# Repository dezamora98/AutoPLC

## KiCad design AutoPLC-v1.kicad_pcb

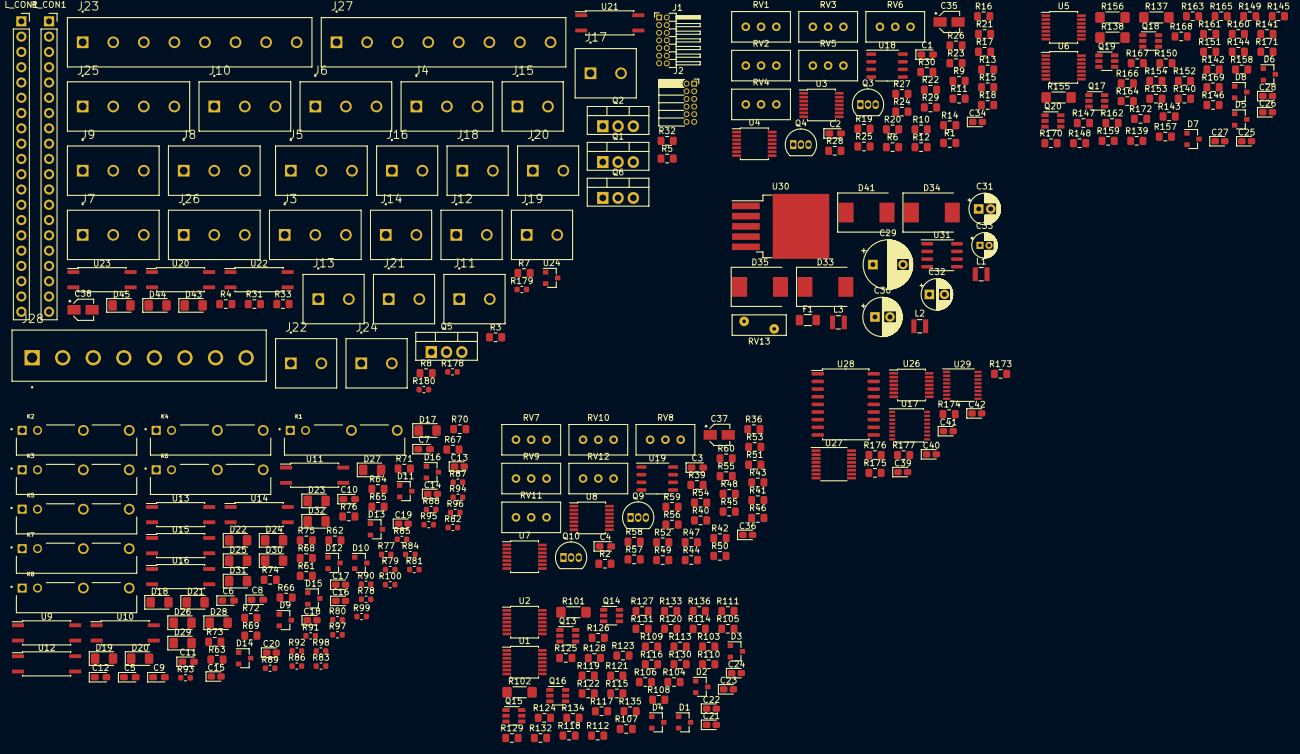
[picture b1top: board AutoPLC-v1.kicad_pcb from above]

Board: 2 copper layers, 358 parts (0 on the bottom side), 318 nets, no tracks yet.

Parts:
C1, C2, C3: 1u; CP_EIA-2012-15_AVX-P_Pad1.30x1.05mm_HandSolder
C4: 2u; CP_EIA-2012-15_AVX-P_Pad1.30x1.05mm_HandSolder
C5, C6, C7, C8, C9, C10, C11, C12: C; CP_EIA-2012-15_AVX-P_Pad1.30x1.05mm_HandSolder
C13, C14, C15, C16, C17, C18, C19, C20: C; CP_EIA-1608-10_AVX-L_Pad1.25x1.05mm_HandSolder
C21, C22, C23, C24, C25, C26, C27, C28: 100n; CP_EIA-1608-10_AVX-L_Pad1.25x1.05mm_HandSolder
C29: 100uF; CP_Radial_D8.0mm_P5.00mm
C30: 220uF; CP_Radial_D6.3mm_P2.50mm
C31: 10uF; CP_Radial_D5.0mm_P2.00mm
C32: 100uF; CP_Radial_D5.0mm_P2.50mm
C33: 10uF; CP_Radial_D4.0mm_P1.50mm
C34, C36, C39, C40, C41, C42: 0.1u; CP_EIA-1608-08_AVX-J_Pad1.25x1.05mm_HandSolder
C35, C37, C38: 10u; CP_Elec_3x5.3
D1, D2, D3, D4, D5, D6, D7, D8: 5v; SOT-23
D9, D10, D11, D12, D13, D14, D15, D16: 1.5; SOT-23
D17, D18, D19, D20, D21, D22, D23, D24, D25, D26, D27, D28, D29, D30, D31, D32: LED; LED_1206_3216Metric_Pad1.42x1.75mm_HandSolder
D33, D34, D35, D41: B360; D_SMC
D43: LED_C; LED_1206_3216Metric_Pad1.42x1.75mm_HandSolder
D44: LED_P; LED_1206_3216Metric_Pad1.42x1.75mm_HandSolder
D45: LED_R; LED_1206_3216Metric_Pad1.42x1.75mm_HandSolder
F1: 3A; Fuse_1206_3216Metric
J1: P_EXP; PinHeader_2x07_P1.27mm_Horizontal
J2: P_ET_MOD; PinSocket_2x06_P1.27mm_Horizontal
J3: AIN_1; BORNERAS_3
J4: AIN_2; BORNERAS_3
J5: AIN_3; BORNERAS_3
J6: AIN_4; BORNERAS_3
J7: AIN_5; BORNERAS_3
J8: AIN_6; BORNERAS_3
J9: AIN_7; BORNERAS_3
J10: AIN_8; BORNERAS_3
J11, J14, J17, J20: AOUT_V; BORNERAS_2
J12, J15, J18, J21: AOUT_C; BORNERAS_2
J13: OUT_T1; BORNERAS_2
J16: OUT_T2; BORNERAS_2
J19: OUT_T3; BORNERAS_2
J22: OUT_T4; BORNERAS_2
J23: DIN; BORNERAS_8
J24: PW_IN; BORNERAS_2
J25: PW & D_COM; BORNERAS_4
J26: PW_OUT_1; BORNERAS_3
J27: R-out; BORNERAS_8
J28: R-out; P_BORNERAS_8
K1, K2, K3, K4, K5, K6, K7, K8: Relay; r
L1, L3: 20uH; L_Wuerth_MAPI-2512
L2: 33uH; L_Wuerth_MAPI-2512
L_CON1: Conn_01x20_Male; PinSocket_1x20_P2.54mm_Vertical
Q1, Q2, Q5, Q6: TIP41; TO-220-3_Vertical
Q3, Q4, Q9, Q10: BC237; TO-92_Inline
Q13, Q14, Q15, Q16, Q17, Q18, Q19, Q20: DMC2400UV; TSOT-23-6
R1, R2, R6, R18, R20, R26, R29, R36, R48, R50, R56, R59, R117, R118, R135, R136, R153, R154, R171, R172: 1k; R_0805_2012Metric_Pad1.15x1.40mm_HandSolder
R3, R4, R5, R7, R69, R70, R71, R72, R73, R74, R75, R76, R114, R116, R132, R134, R150, R152, R168, R170, R173, R174, R175, R176, R177: 5k; R_0805_2012Metric_Pad1.15x1.40mm_HandSolder
R8, R31, R32, R33: 500; R_0805_2012Metric_Pad1.15x1.40mm_HandSolder
R9, R10, R11, R12, R39, R40, R41, R42, R105, R106, R123, R124, R141, R142, R159, R161: 10k; R_0805_2012Metric_Pad1.15x1.40mm_HandSolder
R13, R15, R43, R45: 50k; R_0805_2012Metric_Pad1.15x1.40mm_HandSolder
R14, R16, R21, R22, R23, R24, R25, R27, R28, R30, R44, R46, R51, R52, R53, R54, R55, R57, R58, R60, R107, R108, R109, R110, R125, R126, R127, R128, R143, R144, R145, R146, R160, R162, R163, R164: 100k; R_0805_2012Metric_Pad1.15x1.40mm_HandSolder
R17, R19, R47, R49: 12k; R_0805_2012Metric_Pad1.15x1.40mm_HandSolder
R61, R62, R63, R64, R65, R66, R67, R68: 3k; R_0805_2012Metric_Pad1.15x1.40mm_HandSolder
R77, R78, R79, R80, R81, R82, R83, R84, R85, R86, R87, R88, R89, R90, R91, R92, R93, R94, R95, R96, R97, R98, R99, R100, R178, R179, R180: R; R_0603_1608Metric
R101, R102, R137, R138, R155, R156: 20; R_1806_4516Metric_Pad1.57x1.80mm_HandSolder
R103, R104, R121, R122, R139, R140, R157, R158: 1.3k; R_0805_2012Metric_Pad1.15x1.40mm_HandSolder
R111, R112, R129, R130, R147, R148, R165, R166: 15k; R_0805_2012Metric_Pad1.15x1.40mm_HandSolder
R113, R115, R131, R133, R149, R151, R167, R169: 100; R_0805_2012Metric_Pad1.15x1.40mm_HandSolder
R119, R120: 20; R_0805_2012Metric_Pad1.15x1.40mm_HandSolder
RV1, RV2, RV3, RV4, RV5, RV6, RV7, RV8, RV9, RV10, RV11, RV12: 100; Potentiometer_Bourns_3296W_Vertical
RV13: 30V; RV_Disc_D9mm_W3.4mm_P5mm
R_CON1: Conn_01x20_Male; PinSocket_1x20_P2.54mm_Vertical
U1, U2, U3, U4, U5, U6, U7, U8: LM324; TSSOP-14_4.4x5mm_P0.65mm
U9, U10, U11, U12, U13, U14, U15, U16, U20, U21, U22, U23: LTV-817; SO-4_7.6x3.6mm_P2.54mm
U17: 74HC165; SSOP-16_4.4x5.2mm_P0.65mm
U18, U19: MCP4822; SOP-8_3.9x4.9mm_P1.27mm
U24: REF3033; SOT-23
U26: 74hct125; TSSOP-14_4.4x5mm_P0.65mm
U27: 74HCT595D,118; TSSOP-16_4.4x5mm_P0.65mm
U28: ULN2803A; SOIC-18W_7.5x11.6mm_P1.27mm
U29: 74HCT595D,118; SSOP-16_3.9x4.9mm_P0.635mm
U30: LM2596S-12; TO-263-5_TabPin3
U31: LT1054; SOIC-8_3.9x4.9mm_P1.27mm

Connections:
+3V3: J1.6, J2.1, J2.2, L_CON1.11
+5V: C38.1, J1.7, K1.A1, K2.A1, K3.A1, K4.A1, K5.A1, K6.A1, K7.A1, K8.A1, L_CON1.14, R77.1, R78.1, R79.1, R80.1, R81.1, R82.1, R83.1, R84.1, R85.1, R86.1, R87.1, R88.1, R89.1, R90.1, R91.1, R92.1, U24.1, U28.10
+12V: C32.1, D35.2, J25.4, J26.1, L3.2, U1.4, U2.4, U3.4, U4.4, U5.4, U6.4, U7.4, U8.4, U31.8
+24V: D33.1, D34.1, F1.2, J25.3, J26.2
-12V: C31.2, R13.2, R15.2, R43.2, R45.2, U1.11, U2.11, U3.11, U4.11, U5.11, U6.11, U7.11, U8.11, U31.5
/AIN_C_1: J3.3, R101.2, R105.2
/AIN_C_2: J4.3, R102.2, R106.2
/AIN_C_3: J5.3, R119.2, R123.2
/AIN_C_4: J6.3, R120.2, R124.2
/AIN_C_5: J7.3, R138.2, R142.2
/AIN_C_6: J8.3, R156.2, R161.2
/AIN_C_7: J9.3, R137.2, R141.2
/AIN_C_8: J10.3, R155.2, R159.2
/AIN_Cret_1: J3.2, R101.1
/AIN_Cret_2: J4.2, R102.1
/AIN_Cret_3: J5.2, R119.1
/AIN_Cret_4: J6.2, R120.1
/AIN_Cret_5: J7.2, R138.1
/AIN_Cret_6: J8.2, R156.1
/AIN_Cret_7: J9.2, R137.1
/AIN_Cret_8: J10.2, R155.1
/AIN_V_1: J3.1, R107.2
/AIN_V_2: J4.1, R108.2
/AIN_V_3: J5.1, R125.2
/AIN_V_4: J6.1, R126.2
/AIN_V_5: J7.1, R144.2
/AIN_V_6: J8.1, R162.2
/AIN_V_7: J9.1, R143.2
/AIN_V_8: J10.1, R160.2
/AOUT_C1: J12.2, R25.1, RV5.1
/AOUT_C2: J15.2, R28.1, RV6.1
/AOUT_C3: J18.2, R55.1, RV11.1
/AOUT_C4: J21.2, R58.1, RV12.1
/AOUT_V_1: J11.1, R14.2, RV1.1, U3.1
/AOUT_V_2: J14.1, R16.2, RV2.1, U4.1
/AOUT_V_3: J17.1, R44.2, RV7.1, U7.1
/AOUT_V_4: J20.1, R46.2, RV8.1, U8.1
/A_IN_1: C21.1, D1.1, L_CON1.2, R117.1
/A_IN_2: C22.1, D2.1, L_CON1.3, R118.1
/A_IN_3: C23.1, D3.1, L_CON1.4, R135.1
/A_IN_4: C24.1, D4.1, L_CON1.7, R136.1
/A_IN_5: C26.1, D6.1, L_CON1.8, R154.1
/A_IN_6: C28.1, D8.1, L_CON1.9, R172.1
/A_IN_7: C25.1, D5.1, L_CON1.10, R153.1
/A_IN_8: C27.1, D7.1, R171.1, R_CON1.4
/DIN1: J23.8, R61.2
/DIN2: J23.7, R62.2
/DIN3: J23.6, R63.2
/DIN4: J23.5, R64.2
/DIN5: J23.4, R65.2
/DIN6: J23.3, R66.2
/DIN7: J23.2, R67.2
/DIN8: J23.1, R68.2
/DIO_SPI/SDI_: U17.7, U26.2
/DO1_C1: J27.1, K1.14
/DO1_C2: J28.1, K1.11
/DO2_C1: J27.2, K2.14
/DO2_C2: J28.2, K2.11
/DO3_C1: J27.3, K3.14
/DO3_C2: J28.3, K3.11
/DO4_C1: J27.4, K4.14
/DO4_C2: J28.4, K4.11
/DO5_C1: J27.5, K5.14
/DO5_C2: J28.5, K5.11
/DO6_C1: J27.6, K6.14
/DO6_C2: J28.6, K6.11
/DO7_C1: J27.7, K7.14
/DO7_C2: J28.7, K7.11
/DO8_C1: J27.8, K8.14
/DO8_C2: J28.8, K8.11
/D_COM: C5.2, C6.2, C7.2, C8.2, C9.2, C10.2, C11.2, C12.2, D9.2, D10.2, D11.2, D12.2, D13.2, D14.2, D15.2, D16.2, J25.1, R69.1, R70.1, R71.1, R72.1, R73.1, R74.1, R75.1, R76.1, U9.2, U10.2, U11.2, U12.2, U13.2, U14.2, U15.2, U16.2
/INT_2: R_CON1.6, U26.11
/INT_ET: J2.12, U26.12
/LD: L_CON1.20, U17.1, U18.5, U19.5
/PDIN_1: D17.1, U9.4, U17.11
/PDIN_2: D18.1, U10.4, U17.12
/PDIN_3: D19.1, U11.4, U17.13
/PDIN_4: D20.1, U12.4, U17.14
/PDIN_5: D21.1, U13.4, U17.3
/PDIN_6: D22.1, U14.4, U17.4
/PDIN_7: D23.1, U15.4, U17.5
/PDIN_8: D24.1, U16.4, U17.6
/RO_1: C13.1, D25.1, R93.2, U28.18
/RO_2: C14.1, D26.1, R94.2, U28.17
/RO_3: C15.1, D27.1, R95.2, U28.16
/RO_4: C16.1, D28.1, R96.2, U28.15
/RO_5: C17.1, D29.1, R97.2, U28.14
/RO_6: C18.1, D30.1, R98.2, U28.13
/RO_7: C19.1, D31.1, R99.2, U28.12
/RO_8: C20.1, D32.1, R100.2, U28.11
/RST: J2.8, L_CON1.1, U27.10, U29.10
/SCK: J1.1, J2.9, R_CON1.7, U17.2, U18.3, U19.3, U27.12, U29.12
/SDI: J1.2, R_CON1.8, U26.3, U26.6
/SDI_ET: J2.5, U26.5
/SDO: J1.14, J2.7, R_CON1.15, U18.4, U19.4, U27.14, U29.14
/SEL_A1: R113.2, U29.15
/SEL_A2: R115.2, U29.1
/SEL_A3: R131.2, U29.2
/SEL_A4: R133.2, U29.3
/SEL_A5: R151.2, U29.4
/SEL_A6: R169.2, U29.5
/SEL_A7: R149.2, U29.6
/SEL_A8: R167.2, U29.7
/SS_DA_1: L_CON1.15, U18.2
/SS_DA_2: L_CON1.16, U19.2
/SS_ET: J2.11, R_CON1.20, U26.4
/SS_IO_1: L_CON1.19, U17.15, U26.1, U27.11
/SS_IO_2: R_CON1.19, U29.11
/Terminales/GPIO1: J1.3, L_CON1.6
/Terminales/GPIO2: J1.12, R_CON1.14
/Terminales/GPIO3: J1.4, R_CON1.5
/Terminales/NPN_1: L_CON1.17, R3.2
/Terminales/NPN_2: R4.2, R_CON1.13
/Terminales/NPN_3: R5.2, R_CON1.12
/Terminales/NPN_4: R7.2, R_CON1.11
/Terminales/P_GPIO4: J1.11, R178.2, R_CON1.3
/Terminales/P_GPIO5: J1.5, R179.2, R_CON1.2
/Terminales/P_GPIO6: J1.10, R180.2, R_CON1.1
/Terminales/TX: J1.13, R_CON1.16
/Terminales/VREF: L_CON1.5, U24.2
/VIN_AOUT_C1: J12.1, Q3.1
/VIN_AOUT_C2: J15.1, Q4.1
/VIN_AOUT_C3: J18.1, Q9.1
/VIN_AOUT_C4: J21.1, Q10.1
/Vin: D34.2, J24.2
/Vx: D33.2, D35.1, L_CON1.13
GND: C1.2, C2.2, C3.2, C4.2, C13.2, C14.2, C15.2, C16.2, C17.2, C18.2, C19.2, C20.2, C21.2, C22.2, C23.2, C24.2, C25.2, C26.2, C27.2, C28.2, C29.2, C30.2, C31.1, C32.2, C34.1, C35.1, C36.1, C37.1, C38.2, C39.2, C40.2, C41.2, C42.2, D1.2, D2.2, D3.2, D4.2, D5.2, D6.2, D7.2, D8.2, D41.2, D43.1, D44.1, D45.1, J1.8, J2.3, J2.4, J11.2, J14.2, J17.2, J20.2, J24.1, J25.2, J26.3, L_CON1.12, R9.2, R10.2, R17.1, R18.2, R19.1, R20.2, R39.2, R40.2, R47.1, R48.2, R49.1, R50.2, R103.2, R104.2, R109.1, R110.1, R114.2, R116.2, R121.2, R122.2, R127.1, R128.1, R132.2, R134.2, R139.2, R140.2, R145.1, R146.1, R150.2, R152.2, R157.2, R158.2, R163.1, R164.1, R168.2, R170.2, R173.2, R175.2, R176.2, R177.2, RV13.2, R_CON1.10, U9.3, U10.3, U11.3, U12.3, U13.3, U14.3, U15.3, U16.3, U17.8, U18.7, U19.7, U20.2, U21.2, U22.2, U23.2, U24.3, U26.7, U27.8, U28.9, U29.8, U30.3, U30.5, U31.3
unnamed: C1.1, R1.2, U3.3
unnamed: C2.1, R6.2, U4.3
unnamed: C3.1, R2.2, U7.3
unnamed: C4.1, R36.2, U8.3
unnamed: C5.1, D9.1, R61.1, R69.2, U9.1
unnamed: C6.1, D10.1, R62.1, R70.2, U10.1
unnamed: C7.1, D11.1, R63.1, R71.2, U11.1
unnamed: C8.1, D12.1, R64.1, R72.2, U12.1
unnamed: C9.1, D13.1, R65.1, R73.2, U13.1
unnamed: C10.1, D14.1, R66.1, R74.2, U14.1
unnamed: C11.1, D15.1, R67.1, R75.2, U15.1
unnamed: C12.1, D16.1, R68.1, R76.2, U16.1
unnamed: C29.1, L1.2, U30.1
unnamed: C30.1, L2.2, L3.1, U30.4
unnamed: C33.1, U31.2
unnamed: C33.2, U31.4
unnamed: D17.2, R77.2
unnamed: D18.2, R78.2
unnamed: D19.2, R79.2
unnamed: D20.2, R80.2
unnamed: D21.2, R81.2
unnamed: D22.2, R82.2
unnamed: D23.2, R83.2
unnamed: D24.2, R84.2
unnamed: D25.2, R85.2
unnamed: D26.2, R86.2
unnamed: D27.2, R87.2
unnamed: D28.2, R88.2
unnamed: D29.2, R89.2
unnamed: D30.2, R90.2
unnamed: D31.2, R91.2
unnamed: D32.2, R92.2
unnamed: D41.1, L2.1, U30.2
unnamed: D43.2, R178.1
unnamed: D44.2, R179.1
unnamed: D45.2, R180.1
unnamed: F1.1, L1.1, RV13.1
unnamed: J13.1, Q1.2, R8.1
unnamed: J13.2, Q1.3
unnamed: J16.1, Q2.2, R31.1
unnamed: J16.2, Q2.3
unnamed: J19.1, Q5.2, R32.1
unnamed: J19.2, Q5.3
unnamed: J22.1, Q6.2, R33.1
unnamed: J22.2, Q6.3
unnamed: K1.A2, R93.1
unnamed: K2.A2, R94.1
unnamed: K3.A2, R95.1
unnamed: K4.A2, R96.1
unnamed: K5.A2, R97.1
unnamed: K6.A2, R98.1
unnamed: K7.A2, R99.1
unnamed: K8.A2, R100.1
unnamed: Q1.1, U20.3
unnamed: Q2.1, U21.3
unnamed: Q3.2, R26.1
unnamed: Q3.3, R27.1, RV5.2, RV5.3
unnamed: Q4.2, R29.1
unnamed: Q4.3, R30.1, RV6.2, RV6.3
unnamed: Q5.1, U22.3
unnamed: Q6.1, U23.3
unnamed: Q9.2, R56.1
unnamed: Q9.3, R57.1, RV11.2, RV11.3
unnamed: Q10.2, R59.1
unnamed: Q10.3, R60.1, RV12.2, RV12.3
unnamed: Q13.1, Q13.3, R113.1, R114.1
unnamed: Q13.2, U1.6, U1.7
unnamed: Q13.4, Q13.5, R117.2
unnamed: Q13.6, R111.1, U1.1
unnamed: Q14.1, Q14.3, R115.1, R116.1
unnamed: Q14.2, U1.13, U1.14
unnamed: Q14.4, Q14.5, R118.2
unnamed: Q14.6, R112.1, U1.8
unnamed: Q15.1, Q15.3, R131.1, R132.1
unnamed: Q15.2, U2.6, U2.7
unnamed: Q15.4, Q15.5, R135.2
unnamed: Q15.6, R129.1, U2.1
unnamed: Q16.1, Q16.3, R133.1, R134.1
unnamed: Q16.2, U2.13, U2.14
unnamed: Q16.4, Q16.5, R136.2
unnamed: Q16.6, R130.1, U2.8
unnamed: Q17.1, Q17.3, R149.1, R150.1
unnamed: Q17.2, U5.13, U5.14
unnamed: Q17.4, Q17.5, R153.2
unnamed: Q17.6, R147.1, U5.8
unnamed: Q18.1, Q18.3, R151.1, R152.1
unnamed: Q18.2, U5.6, U5.7
unnamed: Q18.4, Q18.5, R154.2
unnamed: Q18.6, R148.1, U5.1
unnamed: Q19.1, Q19.3, R167.1, R168.1
unnamed: Q19.2, U6.13, U6.14
unnamed: Q19.4, Q19.5, R171.2
unnamed: Q19.6, R165.1, U6.8
unnamed: Q20.1, Q20.3, R169.1, R170.1
unnamed: Q20.2, U6.6, U6.7
unnamed: Q20.4, Q20.5, R172.2
unnamed: Q20.6, R166.1, U6.1
unnamed: R1.1, U18.8
unnamed: R2.1, U19.8
unnamed: R3.1, U20.1
unnamed: R4.1, U21.1
unnamed: R5.1, U22.1
unnamed: R6.1, U18.6
unnamed: R7.1, U23.1
unnamed: R8.2, U20.4
unnamed: R10.1, R12.2, U4.2
unnamed: R11.1, RV1.2, RV1.3
unnamed: R9.1, R11.2, U3.2
unnamed: R12.1, RV2.2, RV2.3
unnamed: R13.1, RV3.1
unnamed: R14.1, R17.2, U3.5
unnamed: R15.1, RV4.1
unnamed: R16.1, R19.2, U4.5
unnamed: R18.1, RV3.3
unnamed: R20.1, RV4.3
unnamed: R21.1, R25.2, U3.10
unnamed: R21.2, U3.6, U3.7
unnamed: R22.1, R27.2, U3.9
unnamed: R22.2, U3.13, U3.14
unnamed: R23.1, R28.2, U4.10
unnamed: R23.2, U4.6, U4.7
unnamed: R24.1, R30.2, U4.9
unnamed: R24.2, U4.13, U4.14
unnamed: R26.2, U3.8
unnamed: R29.2, U4.8
unnamed: R31.2, U21.4
unnamed: R32.2, U22.4
unnamed: R33.2, U23.4
unnamed: R36.1, U19.6
unnamed: R39.1, R41.2, U7.2
unnamed: R40.1, R42.2, U8.2
unnamed: R41.1, RV7.2, RV7.3
unnamed: R42.1, RV8.2, RV8.3
unnamed: R43.1, RV9.1
unnamed: R44.1, R47.2, U7.5
unnamed: R45.1, RV10.1
unnamed: R46.1, R49.2, U8.5
unnamed: R48.1, RV9.3
unnamed: R50.1, RV10.3
unnamed: R51.1, R55.2, U7.10
unnamed: R51.2, U7.6, U7.7
unnamed: R52.1, R57.2, U7.9
unnamed: R52.2, U7.13, U7.14
unnamed: R53.1, R58.2, U8.10
unnamed: R53.2, U8.6, U8.7
unnamed: R54.1, R60.2, U8.9
unnamed: R54.2, U8.13, U8.14
unnamed: R56.2, U7.8
unnamed: R59.2, U8.8
unnamed: R103.1, R111.2, U1.2
unnamed: R104.1, R112.2, U1.10
unnamed: R105.1, U1.3
unnamed: R106.1, U1.9
unnamed: R107.1, R109.2, U1.5
unnamed: R108.1, R110.2, U1.12
unnamed: R121.1, R129.2, U2.2
unnamed: R122.1, R130.2, U2.10
unnamed: R123.1, U2.3
unnamed: R124.1, U2.9
unnamed: R125.1, R127.2, U2.5
unnamed: R126.1, R128.2, U2.12
unnamed: R139.1, R147.2, U5.10
unnamed: R140.1, R148.2, U5.2
unnamed: R141.1, U5.9
unnamed: R142.1, U5.3
unnamed: R143.1, R145.2, U5.12
unnamed: R144.1, R146.2, U5.5
unnamed: R157.1, R165.2, U6.10
unnamed: R158.1, R166.2, U6.2
unnamed: R159.1, U6.9
unnamed: R160.1, R163.2, U6.12
unnamed: R161.1, U6.3
unnamed: R162.1, R164.2, U6.5
unnamed: R173.1, U17.10
unnamed: R174.2, U26.9, U26.10
unnamed: R175.1, U26.13
unnamed: R176.1, U27.13
unnamed: R177.1, U29.13
unnamed: RV3.2, U3.12
unnamed: RV4.2, U4.12
unnamed: RV9.2, U7.12
unnamed: RV10.2, U8.12
unnamed: U27.1, U28.2
unnamed: U27.2, U28.3
unnamed: U27.3, U28.4
unnamed: U27.4, U28.5
unnamed: U27.5, U28.6
unnamed: U27.6, U28.7
unnamed: U27.7, U28.8
unnamed: U27.15, U28.1
VDD: C34.2, C35.2, C36.2, C37.2, C39.1, C40.1, C41.1, C42.1, J1.9, R174.1, R_CON1.9, U17.16, U18.1, U19.1, U26.14, U27.16, U29.16

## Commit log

2023-11-13 add readme
